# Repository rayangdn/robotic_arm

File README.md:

this is a project development of a robotic arm, building from scratch.

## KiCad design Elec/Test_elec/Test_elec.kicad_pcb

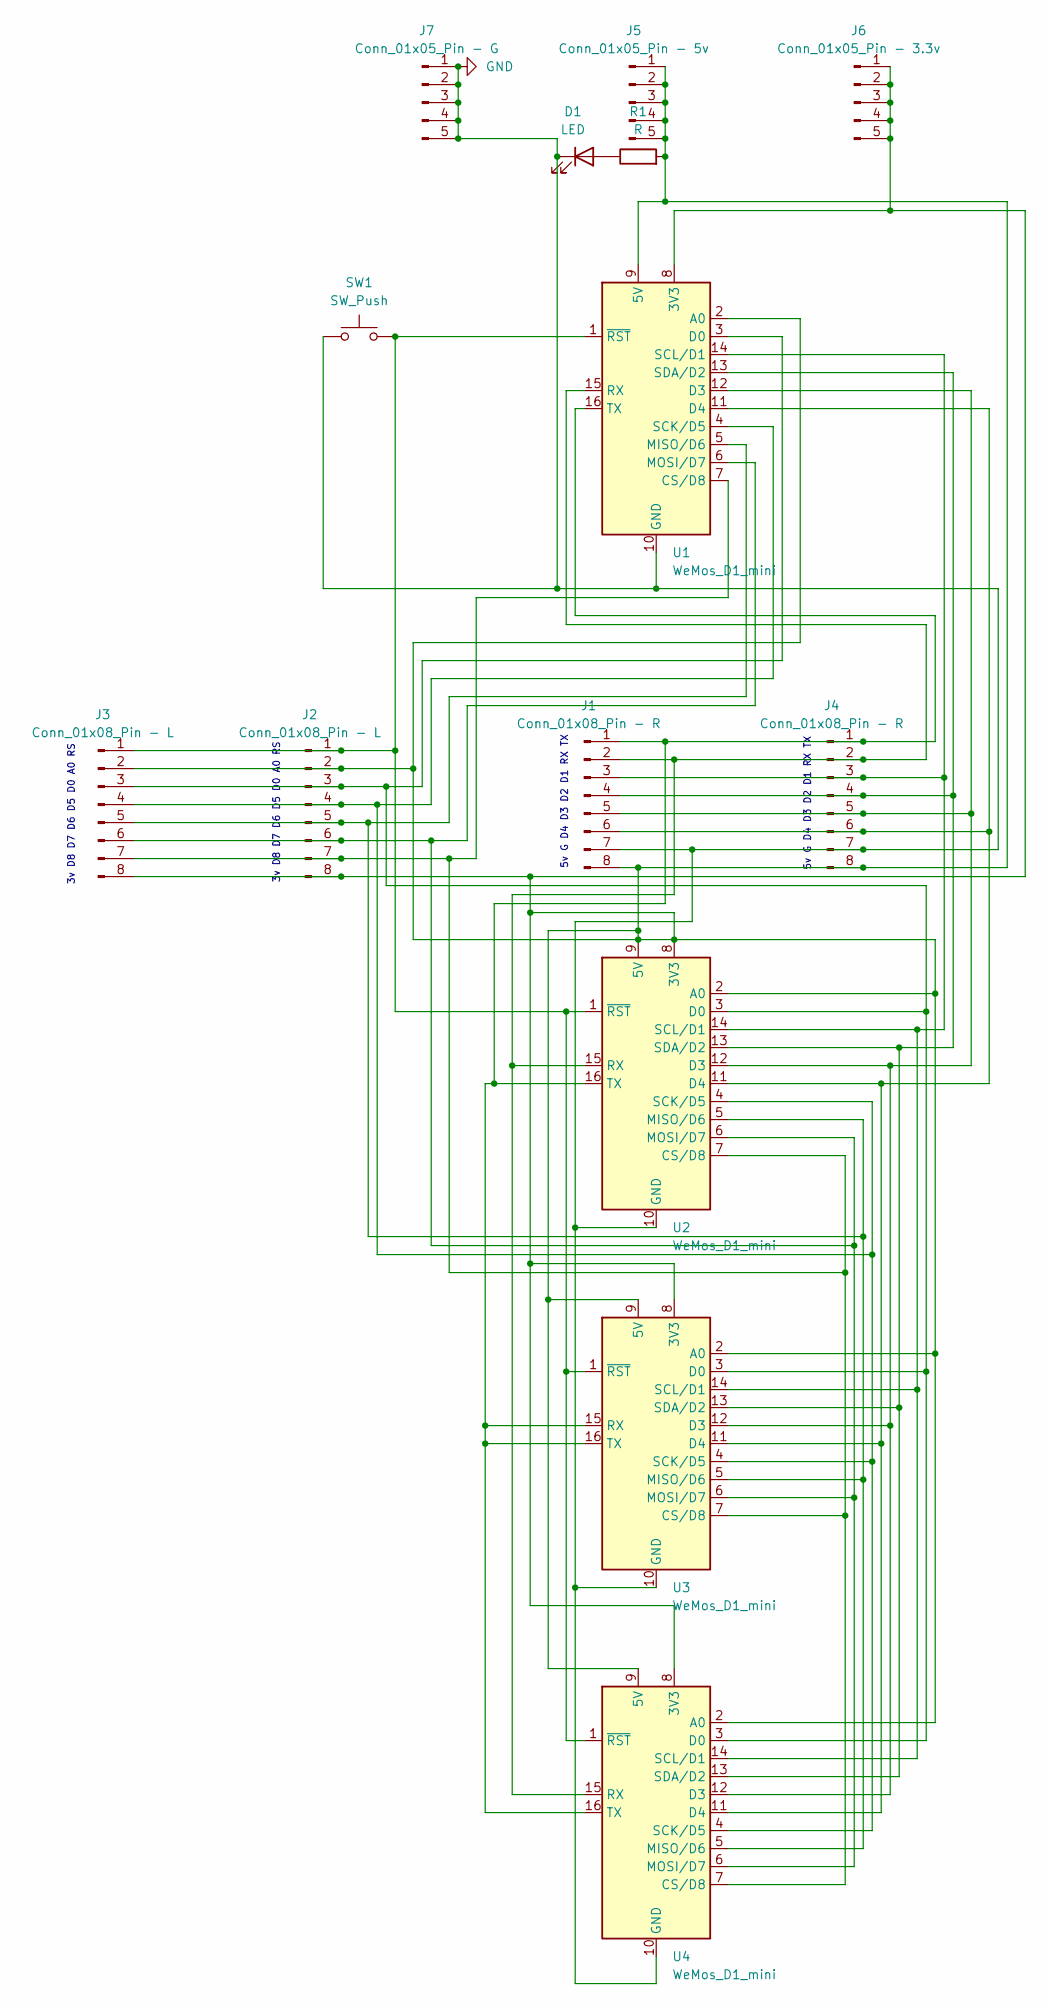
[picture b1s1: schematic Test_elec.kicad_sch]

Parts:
D1: LED; LED_D3.0mm
J1: Conn_01x08_Pin - R; PinHeader_1x08_P2.54mm_Vertical
J2: Conn_01x08_Pin - L; PinHeader_1x08_P2.54mm_Vertical
J3: Conn_01x08_Pin - L; TerminalBlock_RND_205-00018_1x08_P5.00mm_Horizontal
J4: Conn_01x08_Pin - R; TerminalBlock_RND_205-00018_1x08_P5.00mm_Horizontal
J5: Conn_01x05_Pin - 5v; PinSocket_1x05_P2.54mm_Vertical
J6: Conn_01x05_Pin - 3.3v; PinSocket_1x05_P2.54mm_Vertical
J7: Conn_01x05_Pin - G; PinSocket_1x05_P2.54mm_Vertical
R1: R; R_Axial_DIN0207_L6.3mm_D2.5mm_P7.62mm_Horizontal
SW1: SW_Push; SW_PUSH_6mm_H5mm
U1, U2, U3, U4: WeMos_D1_mini; WEMOS_D1_mini_light

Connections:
GND: D1.1 (K), J1.7, J4.7, J7.1, J7.2, J7.3, J7.4, J7.5, SW1.1, U1.10 (GND), U2.10 (GND), U3.10 (GND), U4.10 (GND)
unnamed: D1.2 (A), R1.1
unnamed: J1.1, J4.1, U1.16 (TX), U2.16 (TX), U3.15 (RX), U3.16 (TX), U4.16 (TX)
unnamed: J1.2, J4.2, U1.15 (RX), U2.15 (RX), U4.15 (RX)
unnamed: J1.3, J4.3, U1.14 (SCL/D1), U2.14 (SCL/D1), U3.14 (SCL/D1), U4.14 (SCL/D1)
unnamed: J1.4, J4.4, U1.13 (SDA/D2), U2.13 (SDA/D2), U3.13 (SDA/D2), U4.13 (SDA/D2)
unnamed: J1.5, J4.5, U1.12 (D3), U2.12 (D3), U3.12 (D3), U4.12 (D3)
unnamed: J1.6, J4.6, U1.11 (D4), U2.11 (D4), U3.11 (D4), U4.11 (D4)
unnamed: J1.8, J2.2, J2.8, J3.2, J3.8, J4.8, J5.1, J5.2, J5.3, J5.4, J5.5, J6.1, J6.2, J6.3, J6.4, J6.5, R1.2, U1.2 (A0), U1.8 (3V3), U1.9 (5V), U2.2 (A0), U2.8 (3V3), U2.9 (5V), U3.2 (A0), U3.8 (3V3), U3.9 (5V), U4.2 (A0), U4.8 (3V3), U4.9 (5V)
unnamed: J2.1, J3.1, SW1.2, U1.1 (~RST), U2.1 (~RST), U3.1 (~RST), U4.1 (~RST)
unnamed: J2.3, J3.3, U1.3 (D0), U2.3 (D0), U3.3 (D0), U4.3 (D0)
unnamed: J2.4, J3.4, U1.4 (SCK/D5), U2.4 (SCK/D5), U3.4 (SCK/D5), U4.4 (SCK/D5)
unnamed: J2.5, J3.5, U1.5 (MISO/D6), U2.5 (MISO/D6), U3.5 (MISO/D6), U4.5 (MISO/D6)
unnamed: J2.6, J3.6, U1.6 (MOSI/D7), U2.6 (MOSI/D7), U3.6 (MOSI/D7), U4.6 (MOSI/D7)
unnamed: J2.7, J3.7, U1.7 (CS/D8), U2.7 (CS/D8), U3.7 (CS/D8), U4.7 (CS/D8)

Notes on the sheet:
5v G D4 D3 D2 D1 RX TX
3v D8 D7 D6 D5 D0 A0 RS

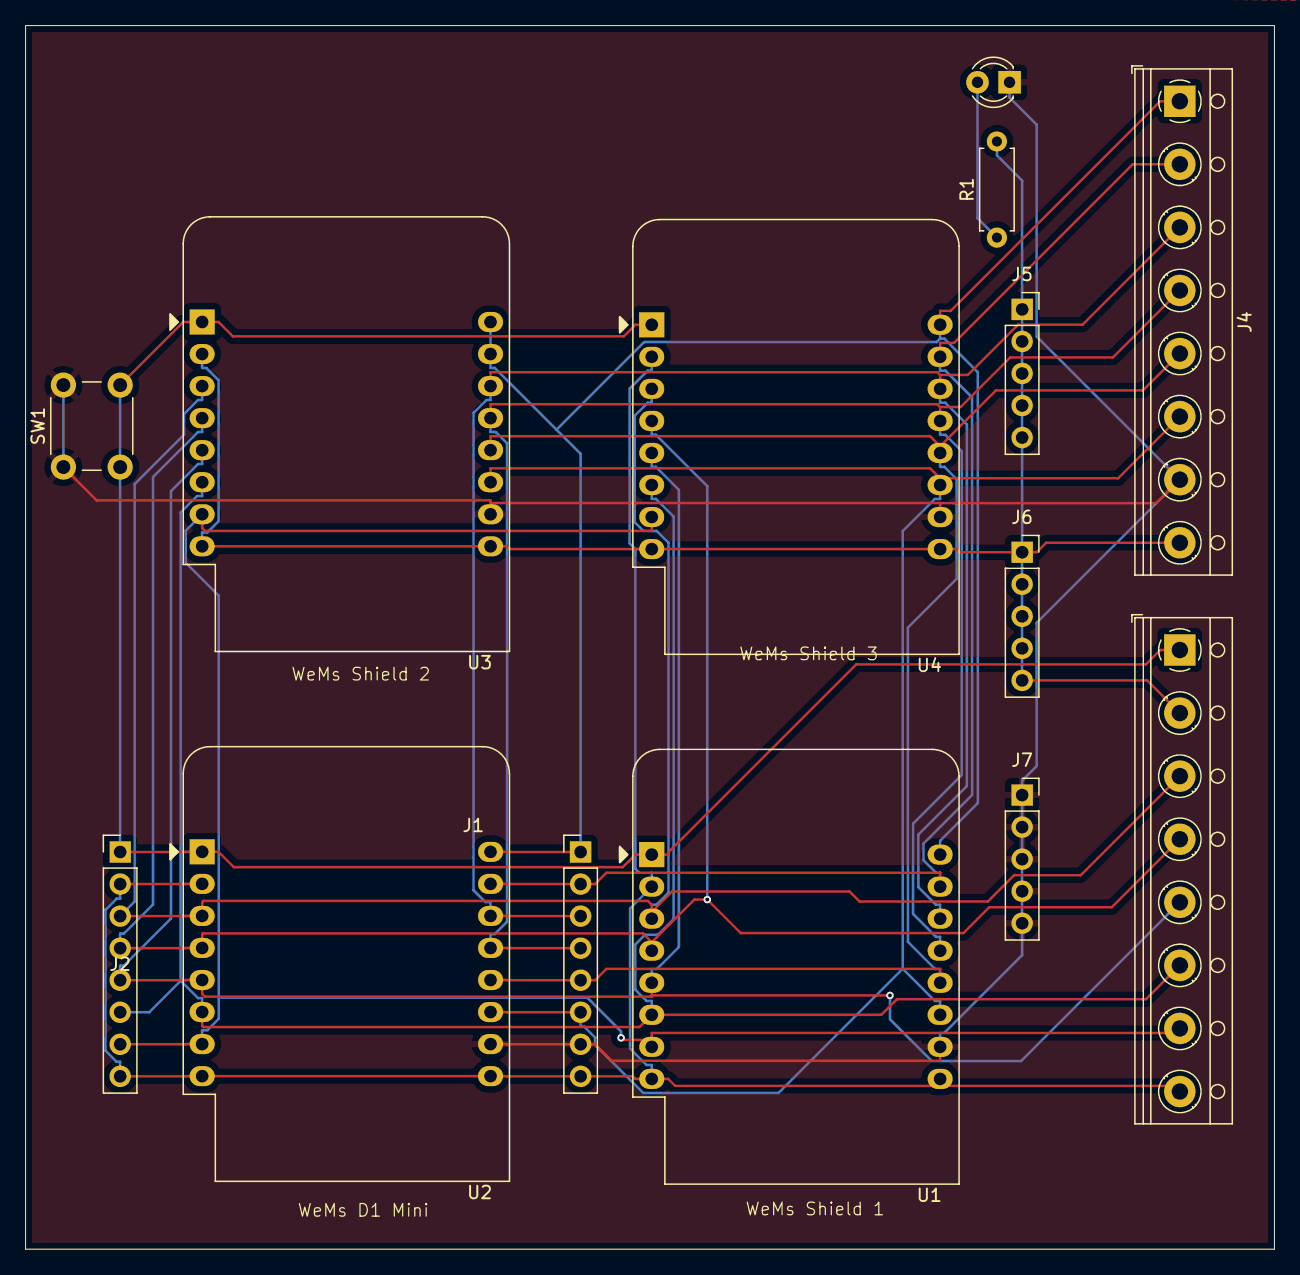
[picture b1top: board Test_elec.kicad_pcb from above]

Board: 2 copper layers, 99.0 x 97.0 mm, 14 parts (0 on the bottom side), 15 nets.

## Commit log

2024-02-10 setup robotic arm on github
2024-02-14 hand cap and shell
2024-02-21 added arm_joint and servo MG... case/cap
2024-02-25 added README file
2024-09-18 first init
